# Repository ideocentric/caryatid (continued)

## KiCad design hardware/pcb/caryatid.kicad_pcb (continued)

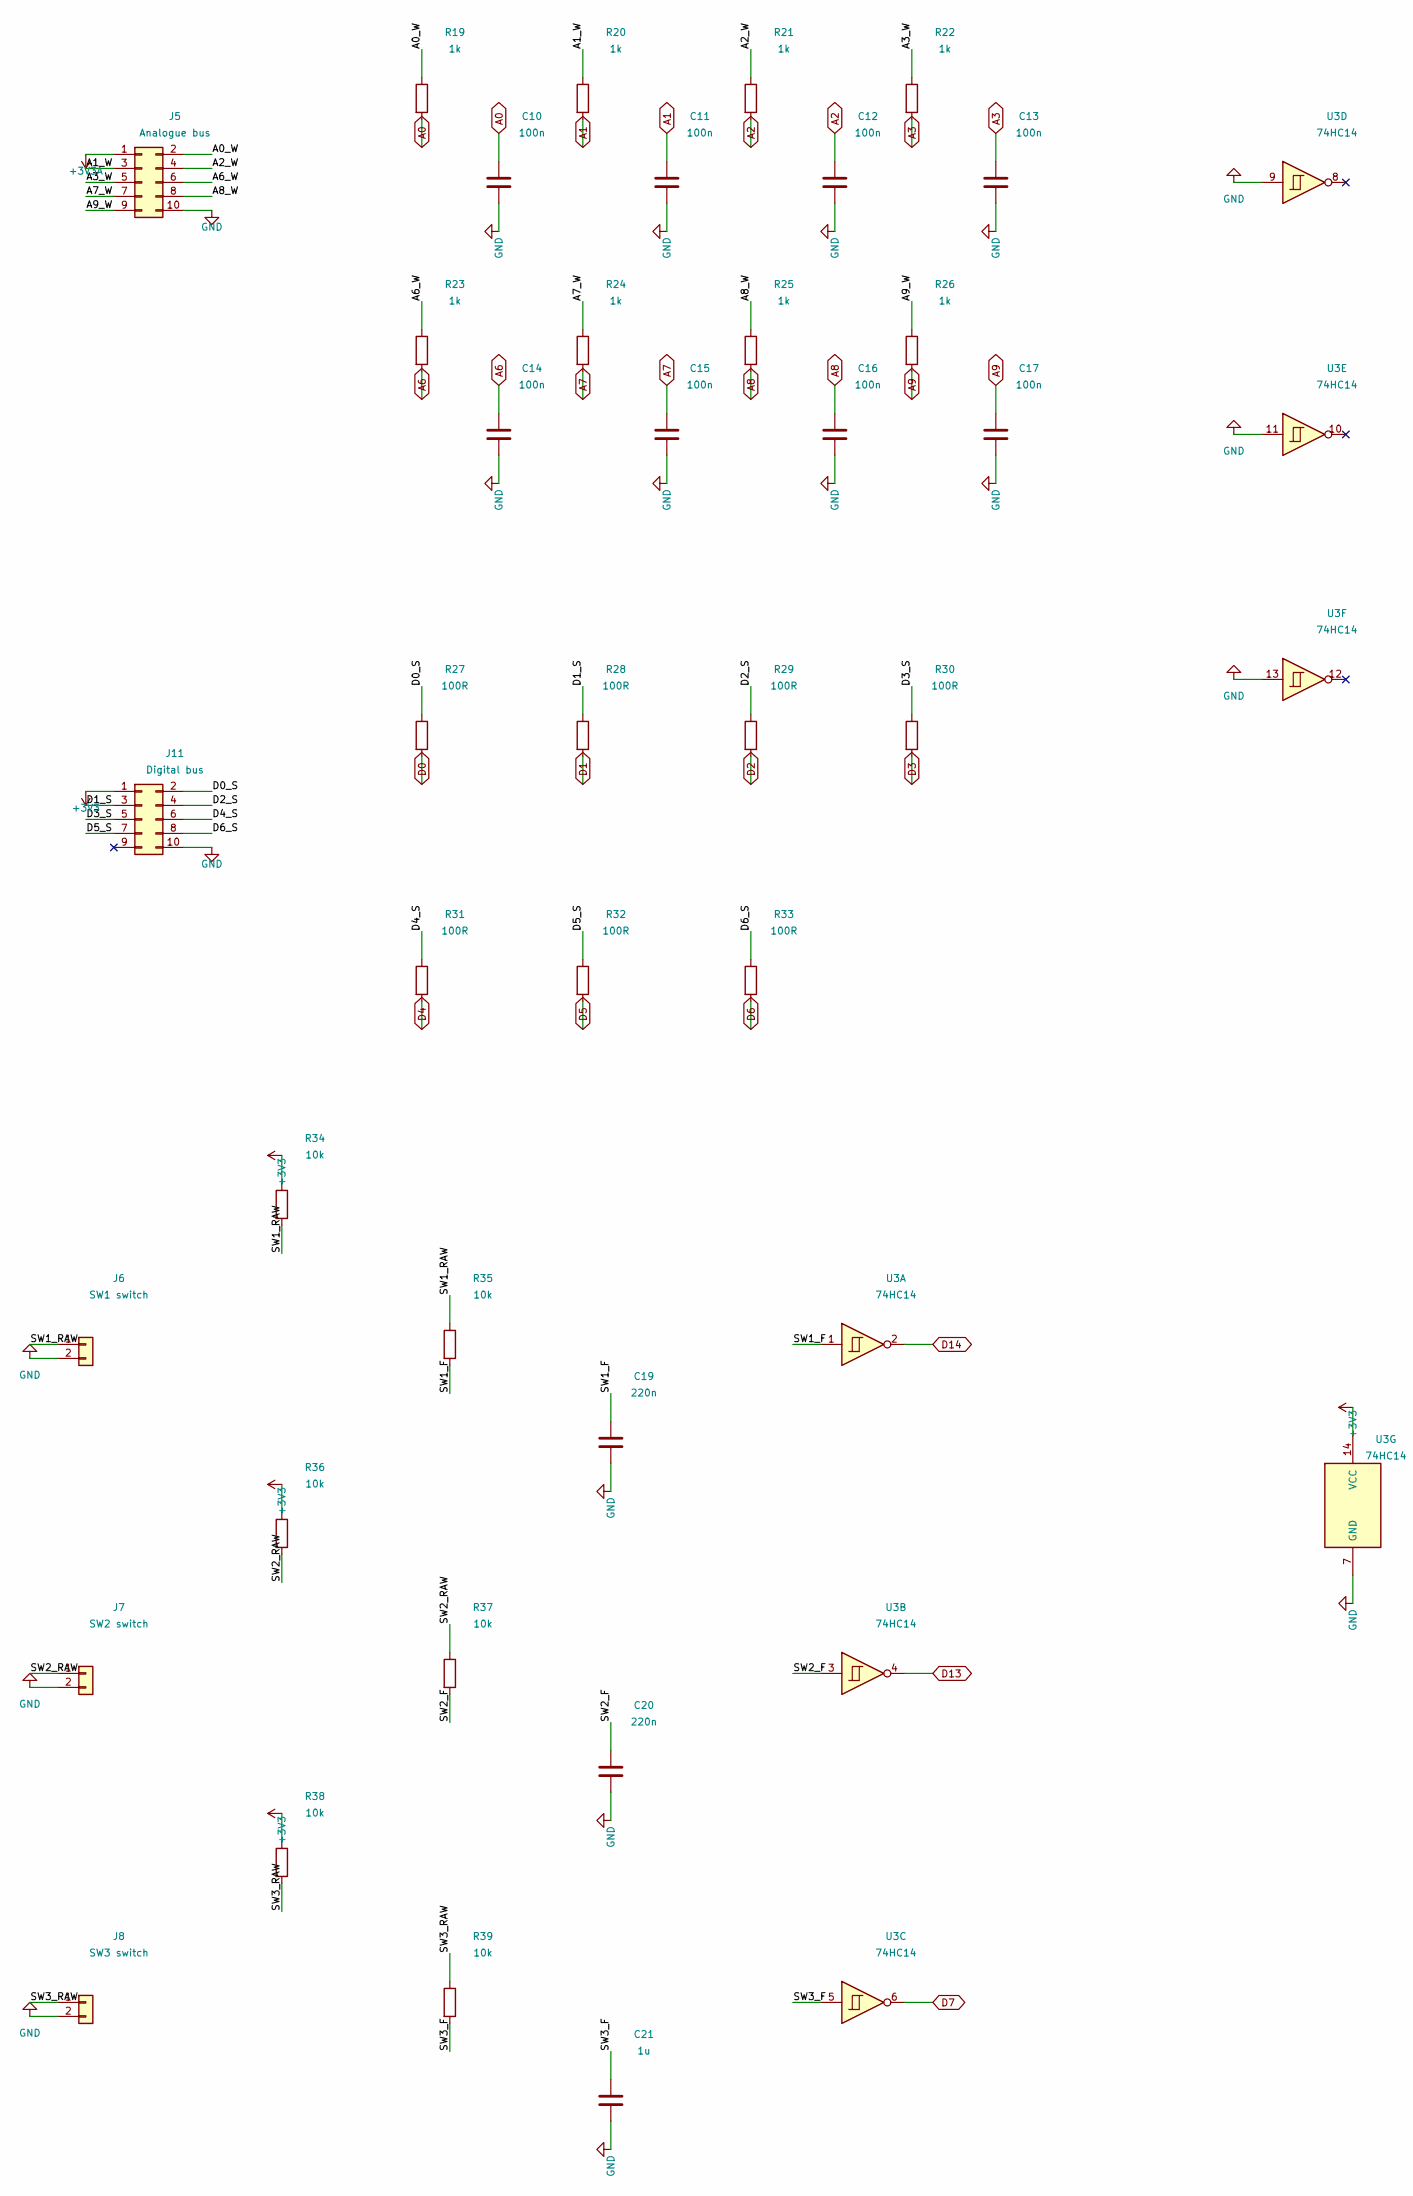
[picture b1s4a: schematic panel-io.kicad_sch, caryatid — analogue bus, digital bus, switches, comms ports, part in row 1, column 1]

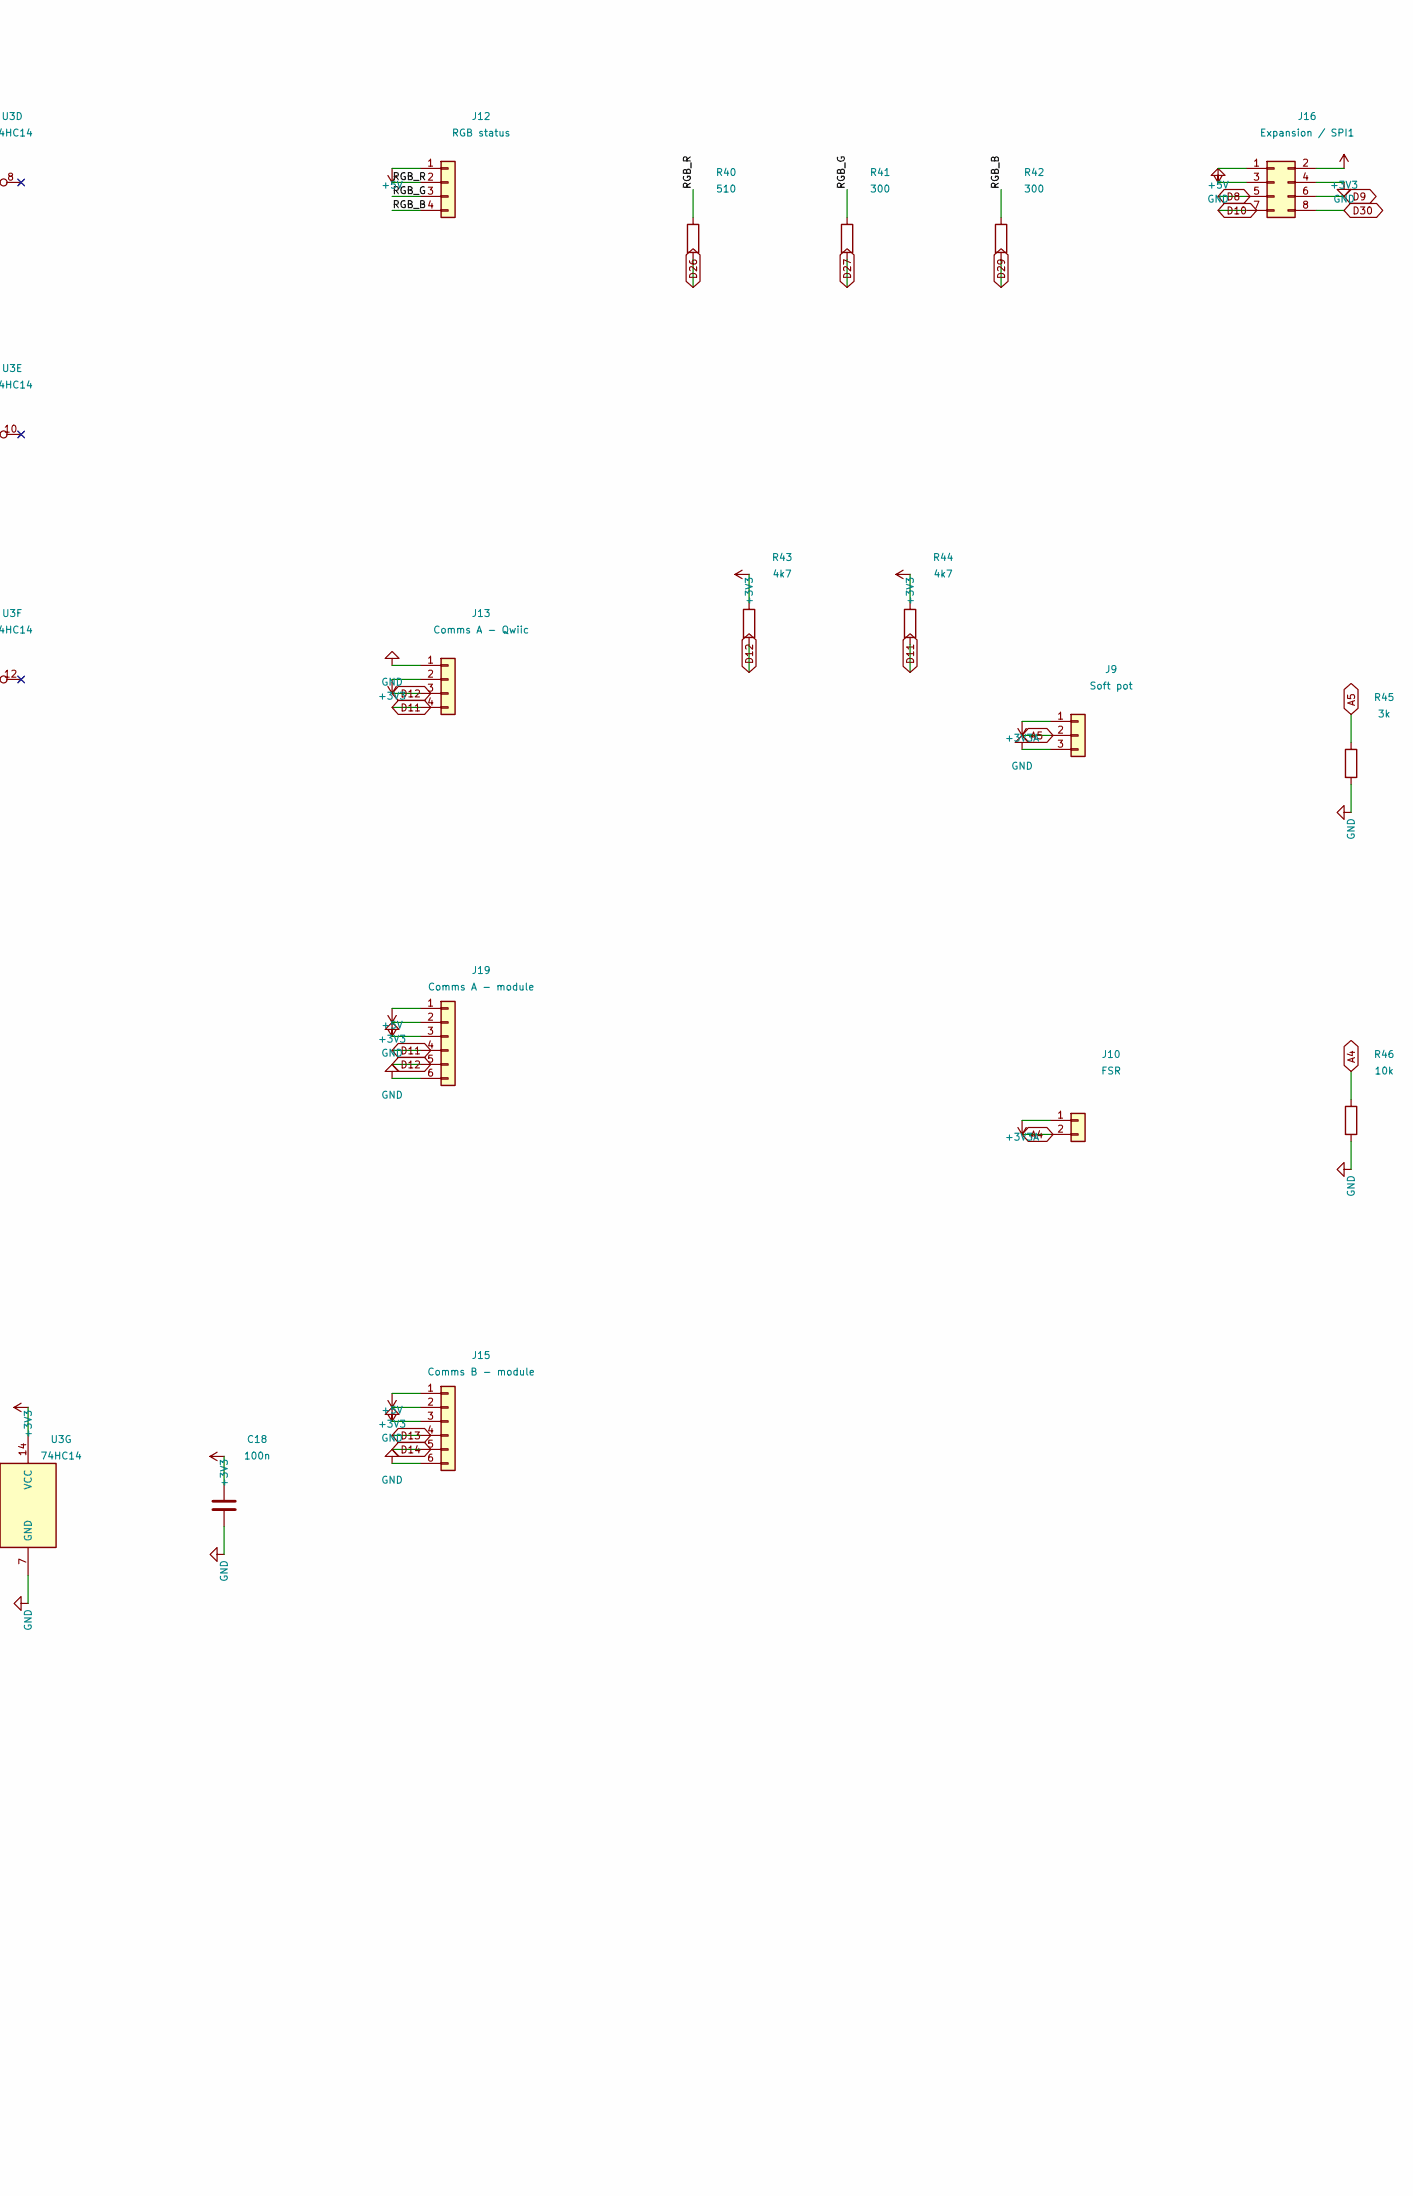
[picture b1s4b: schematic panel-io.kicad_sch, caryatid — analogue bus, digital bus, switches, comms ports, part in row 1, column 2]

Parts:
C10, C11, C12, C13, C14, C15, C16, C17, C18: 100n; C_0603_1608Metric
C19, C20: 220n; C_0603_1608Metric
C21: 1u; C_0603_1608Metric
J5: Analogue bus; IDC-Header_2x05_P2.54mm_Vertical
J6: SW1 switch; JST_XH_B2B-XH-A_1x02_P2.50mm_Vertical
J7: SW2 switch; JST_XH_B2B-XH-A_1x02_P2.50mm_Vertical
J8: SW3 switch; JST_XH_B2B-XH-A_1x02_P2.50mm_Vertical
J9: Soft pot; JST_XH_B3B-XH-A_1x03_P2.50mm_Vertical
J10: FSR; JST_XH_B2B-XH-A_1x02_P2.50mm_Vertical
J11: Digital bus; IDC-Header_2x05_P2.54mm_Vertical
J12: RGB status; JST_XH_B4B-XH-A_1x04_P2.50mm_Vertical
J13: Comms A - Qwiic; JST_SH_SM04B-SRSS-TB_1x04-1MP_P1.00mm_Horizontal
J15: Comms B - module; JST_XH_B6B-XH-A_1x06_P2.50mm_Vertical
J16: Expansion / SPI1; PinHeader_2x04_P2.54mm_Vertical
J19: Comms A - module; JST_XH_B6B-XH-A_1x06_P2.50mm_Vertical
R19, R20, R21, R22, R23, R24, R25, R26: 1k; R_0603_1608Metric
R27, R28, R29, R30, R31, R32, R33: 100R; R_0603_1608Metric
R34, R35, R36, R37, R38, R39, R46: 10k; R_0603_1608Metric
R40: 510; R_0603_1608Metric
R41, R42: 300; R_0603_1608Metric
R43, R44: 4k7; R_0603_1608Metric
R45: 3k; R_0603_1608Metric
U3: 74HC14; SOIC-14_3.9x8.7mm_P1.27mm

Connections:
+3V3: C18.1, J11.1, J13.2, J15.2, J16.2, J19.2, R34.1, R36.1, R38.1, R43.1, R44.1, U3.14 (VCC); also elsewhere on the board
+3V3A: J5.1, J9.1, J10.1; also elsewhere on the board
+5V: J12.1, J15.1, J16.1, J19.1; also elsewhere on the board
/panel-io/A0_W: J5.2, R19.1
/panel-io/A1_W: J5.3, R20.1
/panel-io/A2_W: J5.4, R21.1
/panel-io/A3_W: J5.5, R22.1
/panel-io/A6_W: J5.6, R23.1
/panel-io/A7_W: J5.7, R24.1
/panel-io/A8_W: J5.8, R25.1
/panel-io/A9_W: J5.9, R26.1
/panel-io/D0_S: J11.2, R27.1
/panel-io/D1_S: J11.3, R28.1
/panel-io/D2_S: J11.4, R29.1
/panel-io/D3_S: J11.5, R30.1
/panel-io/D4_S: J11.6, R31.1
/panel-io/D5_S: J11.7, R32.1
/panel-io/D6_S: J11.8, R33.1
/panel-io/RGB_B: J12.4, R42.1
/panel-io/RGB_G: J12.3, R41.1
/panel-io/RGB_R: J12.2, R40.1
/panel-io/SW1_F: C19.1, R35.2, U3.1
/panel-io/SW1_RAW: J6.1, R34.2, R35.1
/panel-io/SW2_F: C20.1, R37.2, U3.3
/panel-io/SW2_RAW: J7.1, R36.2, R37.1
/panel-io/SW3_F: C21.1, R39.2, U3.5
/panel-io/SW3_RAW: J8.1, R38.2, R39.1
A0: C10.1, R19.2; also elsewhere on the board
A1: C11.1, R20.2; also elsewhere on the board
A2: C12.1, R21.2; also elsewhere on the board
A3: C13.1, R22.2; also elsewhere on the board
A4: J10.2, R46.1; also elsewhere on the board
A5: J9.2, R45.1; also elsewhere on the board
A6: C14.1, R23.2; also elsewhere on the board
A7: C15.1, R24.2; also elsewhere on the board
A8: C16.1, R25.2; also elsewhere on the board
A9: C17.1, R26.2; also elsewhere on the board
D0: R27.2; also elsewhere on the board
D1: R28.2; also elsewhere on the board
D2: R29.2; also elsewhere on the board
D3: R30.2; also elsewhere on the board
D4: R31.2; also elsewhere on the board
D5: R32.2; also elsewhere on the board
D6: R33.2; also elsewhere on the board
D7: U3.6; also elsewhere on the board
D8: J16.5; also elsewhere on the board
D9: J16.6; also elsewhere on the board
D10: J16.7; also elsewhere on the board
D11: J13.4, J19.4, R44.2; also elsewhere on the board
D12: J13.3, J19.5, R43.2; also elsewhere on the board
D13: J15.4, U3.4; also elsewhere on the board
D14: J15.5, U3.2; also elsewhere on the board
D26: R40.2; also elsewhere on the board
D27: R41.2; also elsewhere on the board
D29: R42.2; also elsewhere on the board
D30: J16.8; also elsewhere on the board
GND: C10.2, C11.2, C12.2, C13.2, C14.2, C15.2, C16.2, C17.2, C18.2, C19.2, C20.2, C21.2, J5.10, J6.2, J7.2, J8.2, J9.3, J11.10, J13.1, J15.3, J15.6, J16.3, J16.4, J19.3, J19.6, R45.2, R46.2, U3.7 (GND), U3.9, U3.11, U3.13; also elsewhere on the board

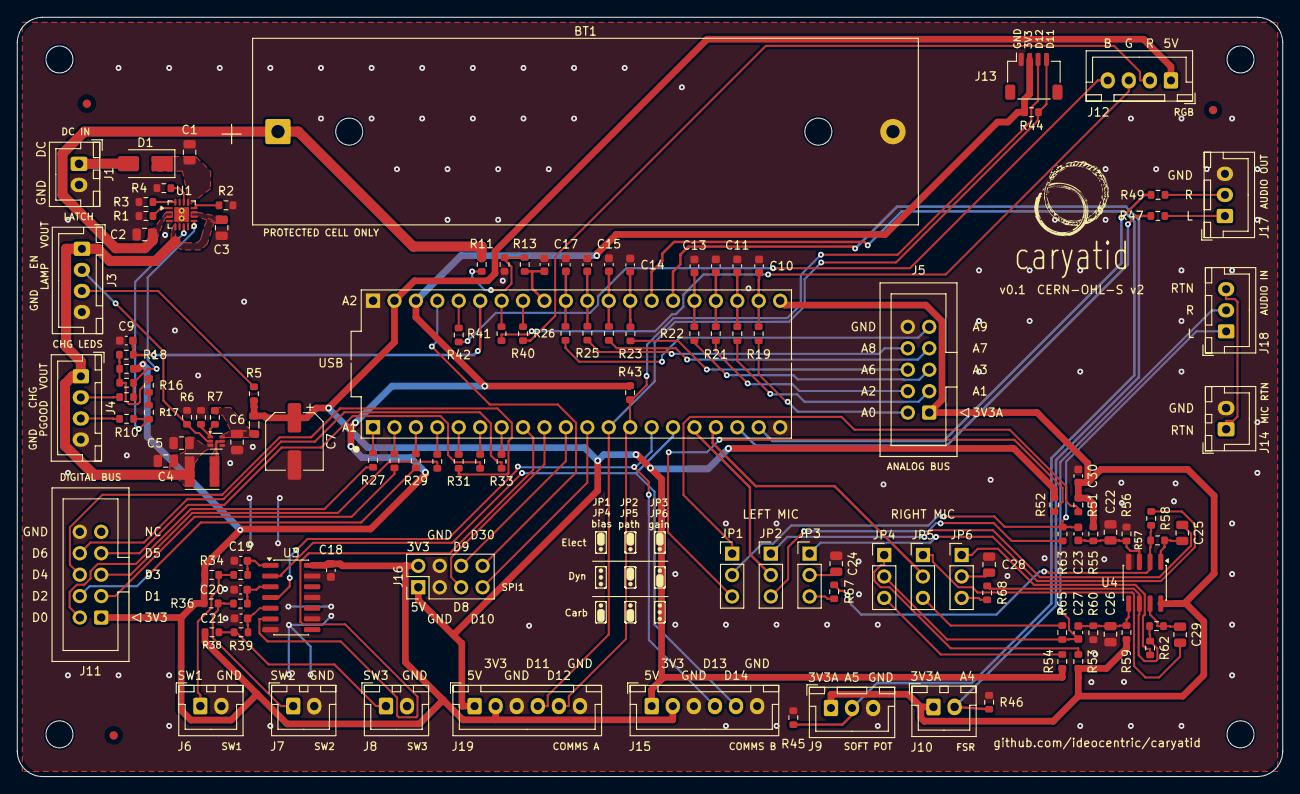
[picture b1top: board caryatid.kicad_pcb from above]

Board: 2 copper layers, 150.0 x 90.0 mm, 135 parts (0 on the bottom side), 108 nets.

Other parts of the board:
FID1, FID2, FID3: Fiducial_1mm_Mask2mm
H1, H2, H3, H4: MountingHole_3.2mm_M3
